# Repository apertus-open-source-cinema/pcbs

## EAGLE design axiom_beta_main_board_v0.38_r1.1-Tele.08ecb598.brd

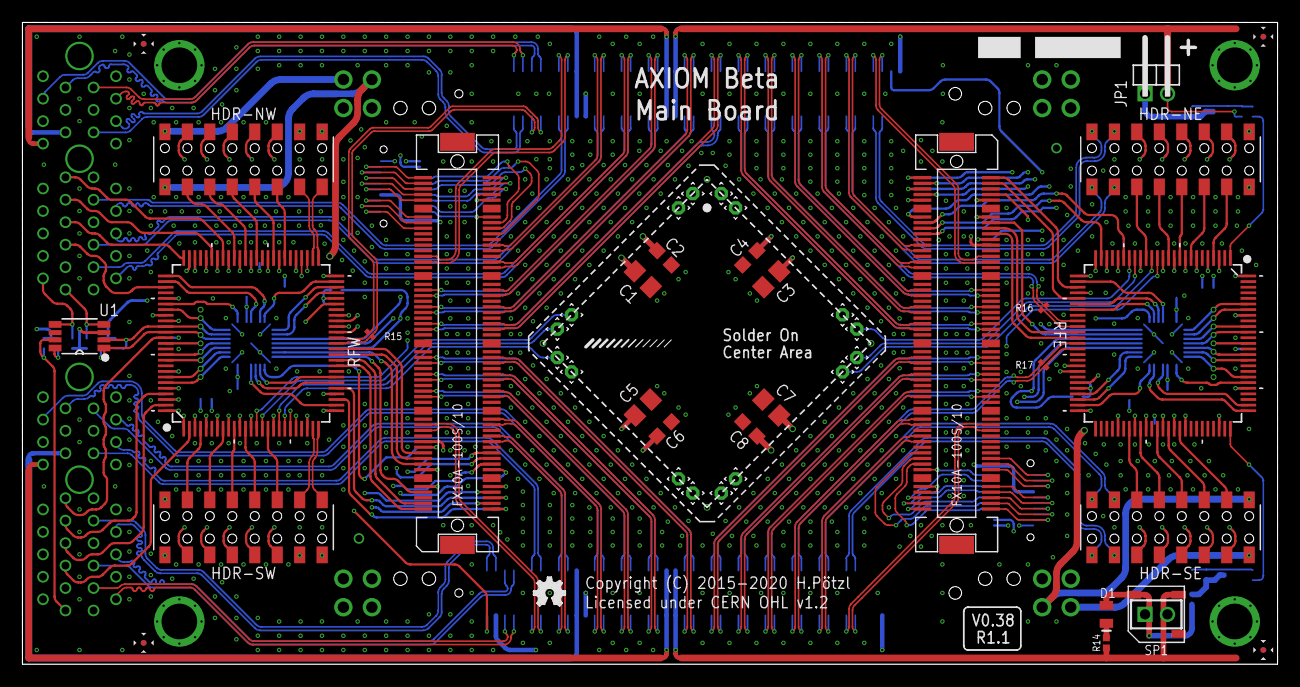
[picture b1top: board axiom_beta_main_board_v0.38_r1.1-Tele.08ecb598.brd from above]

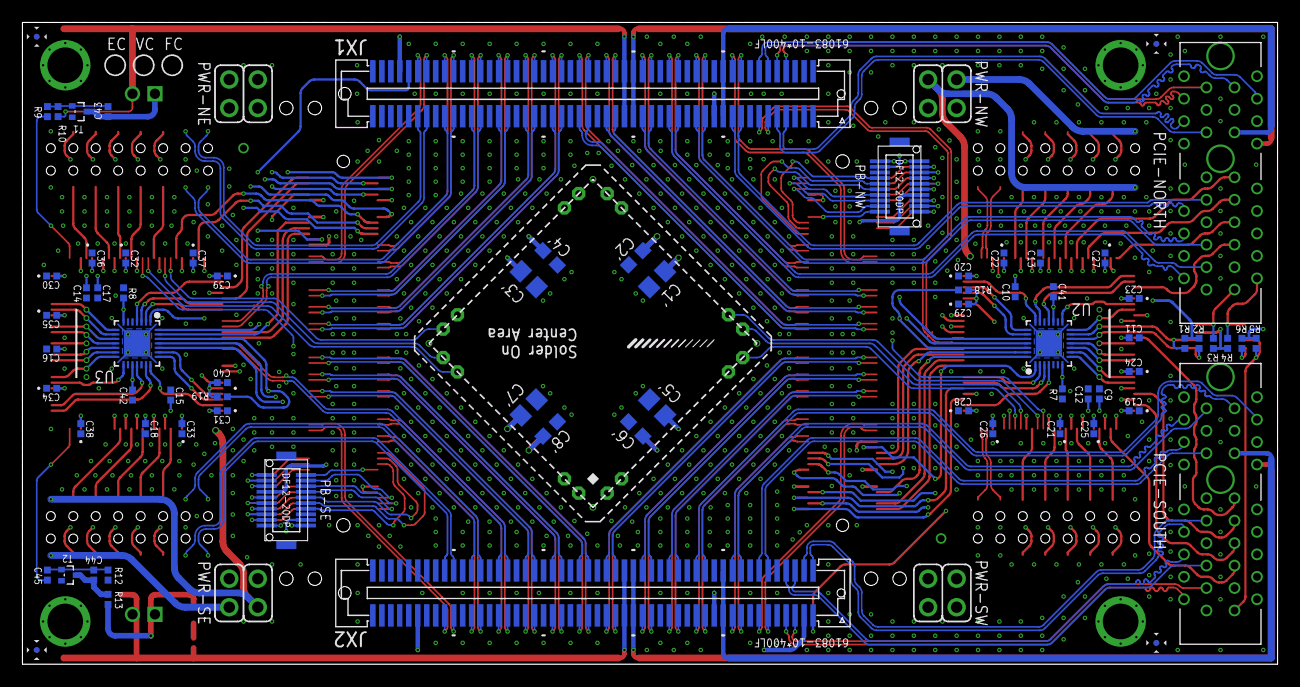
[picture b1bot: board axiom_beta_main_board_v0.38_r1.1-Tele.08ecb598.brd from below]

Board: 4 copper layers, 111.8 x 57.1 mm, 124 parts (78 on the bottom side), 324 nets.

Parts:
C1, C1', C3, C3', C5, C5', C7, C7': 0805-A
C2, C2', C4, C4', C6, C6', C8, C8': 0603-A
C9, C10, C11, C12, C13, C14, C15, C16, C17, C18, C41, C42: 100n; 0402-B
C19, C20, C21, C22, C23, C24, C25, C26, C27, C28, C29, C30, C31, C32, C33, C34, C35, C36, C37, C38, C39, C40, C43, C44: 10n; 0402-B
C45: 1u; 0402-B
D1: DB2S20500L; MICROMELF-R
FID1, FID2, FID3, FID4, FID5, FID6, FID7, FID8: FIDUCIAL; FID_ARROW
HDR-NE: 62101621821
HDR-NW: 62101621821
HDR-SE: 62101621821
HDR-SW: 62101621821
JP1: 1X02M/90-S
JP2: 1X02M
JX1, JX2: BERGSTAK-61083F; 61083-FAKE
LOGO1: OSHW_LOGO_FILLX0100-NT; OSHW_FILLX100_NOTEXT
PAD1, PAD2, PAD3, PAD4, PAD5, PAD6, PAD7, PAD8, PAD9, PAD10, PAD11, PAD12, PAD13, PAD14, PAD15, PAD16: PINPAD1.27MM; 1.2/0.6
PB-NW: DF12(XX)-20DP-0.5V
PB-SE: DF12(XX)-20DP-0.5V
PCIE-NORTH: PCIE-36-AXIOM-NOPEG; PCIE-36-NOPEG
PCIE-SOUTH: PCIE-36-AXIOM-NOPEG; PCIE-36-NOPEG
PWR-NE: PINHD-2X02_2.54; 2X02
PWR-NW: PINHD-2X02_2.54; 2X02
PWR-SE: PINHD-2X02_2.54; 2X02
PWR-SW: PINHD-2X02_2.54; 2X02
R1, R2, R3, R4, R5, R6: 4k7; 0402-B
R7, R8: 50R; 0402-B
R9, R12, R18, R19: 10k; 0402-B
R10: 200k; 0402-B
R13, R14: 12R4; 0402-B
R15, R16, R17: 100R; 0201-B
RFE: MACHXO2-100; MACHXO2-100TQFP
RFW: MACHXO2-100; MACHXO2-100TQFP
SP1: KSSG23J12
T1, T2: NX3008NBKT; SOT416
U1: PCA9540BDP; SOP65P490X300-8N
U2, U3: PIC16F1718-I/MV; QFN40P400X400X55-29N
X-EAST: FX10-100/10S; FX10A-100S/10
X-WEST: FX10-100/10S; FX10A-100S/10
ZED1: µZ-FCI-NOHOLES-R; µZ-NOHOLES-R

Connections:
!E_RESET!: U3.1, X-EAST.19
!SS!_E: RFE.27, U3.4
!SS!_W: RFW.27, U2.4
!W_RESET!: U2.1, X-WEST.19
A_!RST: PB-NW.2, R18.2, U2.26
A_SCL: PB-NW.1, U2.24
A_SDA: PB-NW.3, U2.25
BANK13_00_N: PCIE-NORTH.B17, ZED1.89
BANK13_00_P: PCIE-NORTH.B16, ZED1.87
BANK13_01_N: R15.2, RFW.38, ZED1.90
BANK13_01_P: R15.1, RFW.39, ZED1.88
BANK13_02_N: PCIE-NORTH.A16, ZED1.93
BANK13_02_P: PCIE-NORTH.A17, ZED1.91
BANK13_03_N: PCIE-NORTH.A14, ZED1.94
BANK13_03_P: PCIE-NORTH.A13, ZED1.92
BANK13_04_N: PCIE-SOUTH.A6, ZED1.195
BANK13_04_P: PCIE-SOUTH.A5, ZED1.193
BANK13_05_N: PCIE-SOUTH.A3, ZED1.196
BANK13_05_P: PCIE-SOUTH.A2, ZED1.194
BANK13_06_N: PCIE-SOUTH.A8, ZED1.199
BANK13_06_P: PCIE-SOUTH.A9, ZED1.197
BANK13_SE_0: R7.1, RFW.88, U2.7, ZED1.200
B_!RST: PB-SE.2, R19.2, U3.26
B_SCL: PB-SE.1, U3.24
B_SDA: PB-SE.3, U3.25
CSO_NE_V: C3.1, C3'.1, C4.1, C4'.1, PAD2.1, ZED1.7
CSO_NW_V: C1.1, C1'.1, C2.1, C2'.1, PAD15.1, PWR-NW.1
CSO_SE_V: C7.1, C7'.1, C8.1, C8'.1, PAD7.1, PWR-SE.1
CSO_SW_V: C5.1, C5'.1, C6.1, C6'.1, PAD10.1, ZED1.112
C_CK_E: PAD5.1, RFE.18
C_CK_W: PAD13.1, RFW.18
C_EN_E: PAD3.1, RFE.14
C_EN_W: PAD11.1, RFW.14
C_SI_E: PAD4.1, RFE.19
C_SI_W: PAD12.1, RFW.19
C_SO_E: PAD6.1, RFE.15
C_SO_W: PAD14.1, RFW.15
DONE_E: RFE.76, U3.20
DONE_W: RFW.76, U2.20
E_EN: RFE.20, X-EAST.14
E_I2C_EN: U3.27, X-EAST.13
E_I2C_V: PWR-NE.1, X-EAST.11
E_SCK: RFE.21, X-EAST.12
E_SCL: RFE.36, X-EAST.15
E_SDA: RFE.37, X-EAST.17
E_SDI: RFE.24, X-EAST.16
E_SDO: RFE.25, X-EAST.18
E_SPI_V: PWR-NE.3, X-EAST.21
E_VE_CV: PB-SE.19, X-EAST.90
E_VE_OV: PB-SE.10, X-EAST.93
E_VE_UV: PB-SE.12, X-EAST.91
GND: C1.2, C1'.2, C2.2, C2'.2, C3.2, C3'.2, C4.2, C4'.2, C5.2, C5'.2, C6.2, C6'.2, C7.2, C7'.2, C8.2, C8'.2, C9.2, C10.2, C11.2, C12.2, C13.2, C14.2, C15.2, C16.2, C17.2, C18.2, C19.2, C20.2, C21.2, C22.2, C23.2, C24.2, C25.2, C26.2, C27.2, C28.2, C29.2, C30.2, C31.2, C32.2, C33.2, C34.2, C35.2, C36.2, C37.2, C38.2, C39.2, C40.2, C41.2, C42.2, HDR-NE.1, HDR-NE.2, HDR-SW.1, HDR-SW.2, PAD1.1, PAD8.1, PAD9.1, PAD16.1, PB-NW.5, PB-SE.5, PCIE-NORTH.A1, PCIE-NORTH.A4, PCIE-NORTH.A7, PCIE-NORTH.A10, PCIE-NORTH.A12, PCIE-NORTH.A15, PCIE-NORTH.A18, PCIE-NORTH.B15, PCIE-NORTH.B18, PCIE-SOUTH.A1, PCIE-SOUTH.A4, PCIE-SOUTH.A7, PCIE-SOUTH.A10, PCIE-SOUTH.A12, PCIE-SOUTH.A15, PCIE-SOUTH.A18, PCIE-SOUTH.B15, PCIE-SOUTH.B18, R7.2, R8.2, R12.1, RFE.6, RFE.22, RFE.33, RFE.44, RFE.56, RFE.72, RFE.79, RFE.92, RFW.6, RFW.22, RFW.33, RFW.44, RFW.56, RFW.72, RFW.79, RFW.92, T1.2, T2.2, U1.6, U2.5, U2.16, U2.29, U3.5, U3.16, U3.29, X-EAST.5, X-EAST.20, X-EAST.23, X-EAST.26, X-EAST.29, X-EAST.31, X-EAST.32, X-EAST.37, X-EAST.38, X-EAST.43, X-EAST.44, X-EAST.49, X-EAST.50, X-EAST.51, X-EAST.52, X-EAST.57, X-EAST.58, X-EAST.63, X-EAST.64, X-EAST.69, X-EAST.70, X-EAST.71, X-EAST.76, X-EAST.77, X-EAST.82, X-EAST.G1, X-EAST.G2, X-EAST.G3, X-EAST.G4, X-EAST.G5, X-EAST.G6, X-EAST.G7, X-EAST.G8, X-EAST.G9, X-EAST.G10, X-WEST.5, X-WEST.20, X-WEST.23, X-WEST.26, X-WEST.29, X-WEST.31, X-WEST.32, X-WEST.37, X-WEST.38, X-WEST.43, X-WEST.44, X-WEST.49, X-WEST.50, X-WEST.51, X-WEST.52, X-WEST.57, X-WEST.58, X-WEST.63, X-WEST.64, X-WEST.69, X-WEST.70, X-WEST.71, X-WEST.76, X-WEST.77, X-WEST.82, X-WEST.G1, X-WEST.G2, X-WEST.G3, X-WEST.G4, X-WEST.G5, X-WEST.G6, X-WEST.G7, X-WEST.G8, X-WEST.G9, X-WEST.G10, ZED1.15, ZED1.16, ZED1.21, ZED1.22, ZED1.27, ZED1.28, ZED1.33, ZED1.34, ZED1.39, ZED1.40, ZED1.45, ZED1.46, ZED1.51, ZED1.52, ZED1.65, ZED1.66, ZED1.71, ZED1.72, ZED1.77, ZED1.85, ZED1.86, ZED1.95, ZED1.96, ZED1.115, ZED1.116, ZED1.121, ZED1.122, ZED1.127, ZED1.128, ZED1.133, ZED1.134, ZED1.139, ZED1.140, ZED1.145, ZED1.146, ZED1.151, ZED1.152, ZED1.165, ZED1.166, ZED1.171, ZED1.172, ZED1.177, ZED1.185, ZED1.186, ZED1.191, ZED1.192
INITN_E: RFE.77, U3.18
INITN_W: RFW.77, U2.18
IO_SCL: RFE.86, U3.12
IO_SDA: RFE.85, U3.13
JTAGENB_E: RFE.82, U3.14
JTAGENB_W: RFW.82, U2.14
JTAG_V: PWR-SW.3, X-WEST.21
JX1_00_N: X-EAST.27, ZED1.13
JX1_00_P: X-EAST.25, ZED1.11
JX1_01_N: HDR-NE.13, ZED1.14
JX1_01_P: HDR-NE.15, ZED1.12
JX1_02_N: X-EAST.24, ZED1.19
JX1_02_P: X-EAST.22, ZED1.17
JX1_03_N: HDR-NE.14, ZED1.20
JX1_03_P: HDR-NE.16, ZED1.18
JX1_04_N: X-EAST.30, ZED1.25
JX1_04_P: X-EAST.28, ZED1.23
JX1_05_N: R16.2, RFE.35, ZED1.26
JX1_05_P: R16.1, RFE.34, ZED1.24
JX1_06_N: X-EAST.36, ZED1.31
JX1_06_P: X-EAST.34, ZED1.29
JX1_07_N: X-EAST.35, ZED1.32
JX1_07_P: X-EAST.33, ZED1.30
JX1_08_N: X-EAST.42, ZED1.37
JX1_08_P: X-EAST.40, ZED1.35
JX1_09_N: X-EAST.41, ZED1.38
JX1_09_P: X-EAST.39, ZED1.36
JX1_10_N: X-EAST.48, ZED1.43
JX1_10_P: X-EAST.46, ZED1.41
JX1_11_N: X-EAST.47, ZED1.44
JX1_11_P: X-EAST.45, ZED1.42
JX1_12_N: X-WEST.56, ZED1.49
JX1_12_P: X-WEST.54, ZED1.47
JX1_13_N: X-WEST.55, ZED1.50
JX1_13_P: X-WEST.53, ZED1.48
JX1_14_N: X-WEST.62, ZED1.55
JX1_14_P: X-WEST.60, ZED1.53
JX1_15_N: X-WEST.61, ZED1.56
JX1_15_P: X-WEST.59, ZED1.54
JX1_16_N: X-WEST.68, ZED1.63
JX1_16_P: X-WEST.66, ZED1.61
JX1_17_N: X-WEST.67, ZED1.64
JX1_17_P: X-WEST.65, ZED1.62
JX1_18_N: X-WEST.74, ZED1.69
JX1_18_P: X-WEST.72, ZED1.67
JX1_19_N: PCIE-NORTH.A3, ZED1.70
JX1_19_P: PCIE-NORTH.A2, ZED1.68
JX1_20_N: X-WEST.80, ZED1.75
JX1_20_P: X-WEST.78, ZED1.73
JX1_21_N: PCIE-NORTH.A6, ZED1.76
JX1_21_P: PCIE-NORTH.A5, ZED1.74
JX1_22_N: X-WEST.75, ZED1.83
JX1_22_P: X-WEST.73, ZED1.81
JX1_23_N: PCIE-NORTH.A9, ZED1.84
JX1_23_P: PCIE-NORTH.A8, ZED1.82
JX1_SE_0: R8.1, RFE.88, U3.7, ZED1.9
JX2_00_N: HDR-SE.14, ZED1.119
JX2_00_P: HDR-SE.16, ZED1.117
JX2_01_N: X-EAST.73, ZED1.120
JX2_01_P: X-EAST.75, ZED1.118
JX2_02_N: HDR-SE.13, ZED1.125
JX2_02_P: HDR-SE.15, ZED1.123
JX2_03_N: X-EAST.78, ZED1.126
JX2_03_P: X-EAST.80, ZED1.124
JX2_04_N: R17.1, RFE.38, ZED1.131
JX2_04_P: R17.2, RFE.39, ZED1.129
JX2_05_N: X-EAST.72, ZED1.132
JX2_05_P: X-EAST.74, ZED1.130
JX2_06_N: X-EAST.65, ZED1.137
JX2_06_P: X-EAST.67, ZED1.135
JX2_07_N: X-EAST.66, ZED1.138
JX2_07_P: X-EAST.68, ZED1.136
JX2_08_N: X-EAST.59, ZED1.143
JX2_08_P: X-EAST.61, ZED1.141
JX2_09_N: X-EAST.60, ZED1.144
JX2_09_P: X-EAST.62, ZED1.142
JX2_10_N: X-EAST.53, ZED1.149
JX2_10_P: X-EAST.55, ZED1.147
JX2_11_N: X-EAST.54, ZED1.150
JX2_11_P: X-EAST.56, ZED1.148
JX2_12_N: X-WEST.45, ZED1.155
JX2_12_P: X-WEST.47, ZED1.153
JX2_13_N: X-WEST.46, ZED1.156
JX2_13_P: X-WEST.48, ZED1.154
JX2_14_N: X-WEST.39, ZED1.163
JX2_14_P: X-WEST.41, ZED1.161
JX2_15_N: X-WEST.40, ZED1.164
JX2_15_P: X-WEST.42, ZED1.162
JX2_16_N: X-WEST.33, ZED1.169
JX2_16_P: X-WEST.35, ZED1.167
JX2_17_N: X-WEST.34, ZED1.170
JX2_17_P: X-WEST.36, ZED1.168
JX2_18_N: PCIE-SOUTH.B17, ZED1.175
JX2_18_P: PCIE-SOUTH.B16, ZED1.173
JX2_19_N: X-WEST.28, ZED1.176
JX2_19_P: X-WEST.30, ZED1.174
JX2_20_N: PCIE-SOUTH.A17, ZED1.183
JX2_20_P: PCIE-SOUTH.A16, ZED1.181
JX2_21_N: X-WEST.22, ZED1.184
JX2_21_P: X-WEST.24, ZED1.182
JX2_22_N: PCIE-SOUTH.A13, ZED1.189
JX2_22_P: PCIE-SOUTH.A14, ZED1.187
JX2_23_N: X-WEST.25, ZED1.190
JX2_23_P: X-WEST.27, ZED1.188
unnamed: C43.2, JP1.1, T1.3
unnamed: C44.2, R13.1, T2.3
unnamed: D1.C, R14.1
unnamed: D1.A, JP2.1, R13.2, SP1.2
unnamed: C43.1, R9.2, R10.2, T1.1
unnamed: C44.1, C45.1, R12.2, T2.1
N_CHK_V: PB-NW.14, X-WEST.92
N_I2C_EN: U3.28, X-EAST.7
N_I2C_V: PWR-NE.4, X-EAST.9
N_IO0: R9.1, RFE.1
N_SCK: RFE.42, X-EAST.2
N_SCL: RFE.28, X-EAST.1
N_SDA: RFE.30, X-EAST.3
N_SDI: RFE.29, X-EAST.6
N_SDO: RFE.43, X-EAST.4
N_SPI_EN: RFE.45, X-EAST.8
N_SPI_V: PWR-NE.2, X-EAST.10
N_VE_CV: PB-NW.17, X-WEST.96
N_VE_OV: PB-NW.8, X-WEST.95
N_VE_RS: PB-NW.7, X-WEST.88
N_VE_UV: PB-NW.20, X-WEST.85
N_VN_CV: PB-NW.15, X-WEST.98
N_VN_OV: PB-NW.6, X-WEST.97
N_VN_RS: PB-NW.11, X-WEST.86
N_VN_UV: PB-NW.18, X-WEST.87
N_VW_CV: PB-NW.13, X-WEST.100
N_VW_OV: PB-NW.4, X-WEST.99
N_VW_RS: PB-NW.9, X-WEST.84
N_VW_UV: PB-NW.16, X-WEST.89
PB22B_E: RFE.47, U3.23
PB22B_W: RFW.47, U2.23
PCIE_I2C_V: PCIE-NORTH.B3, PCIE-SOUTH.B3, R3.1, R4.1, R5.1, R6.1, U1.3, ZED1.198
PCIE_N_5V: PCIE-NORTH.B12, ZED1.59, ZED1.60
PCIE_N_IO0: PCIE-NORTH.B4, RFW.83
PCIE_N_IO1: PCIE-NORTH.B5, RFW.78
PCIE_N_IO2: PCIE-NORTH.B6, RFW.74
PCIE_N_IO3: PCIE-NORTH.B7, RFW.75
PCIE_N_IO4: PCIE-NORTH.B8, RFW.71
PCIE_N_IO5: PCIE-NORTH.B9, RFW.70
PCIE_N_IO6: PCIE-NORTH.B10, RFW.69
PCIE_N_IO7: PCIE-NORTH.B11, RFW.68
PCIE_N_SCL: PCIE-NORTH.B2, R4.2, U1.5
PCIE_N_SDA: PCIE-NORTH.B1, R3.2, U1.4
PCIE_N_V: PCIE-NORTH.B13, ZED1.79, ZED1.80
PCIE_N_VCCIO: PCIE-NORTH.B14, ZED1.78
PCIE_SCL: R2.2, RFW.86, U1.1, U2.12
PCIE_SDA: R1.2, RFW.85, U1.2, U2.13
PCIE_S_5V: PCIE-SOUTH.B12, ZED1.159, ZED1.160
PCIE_S_IO0: PCIE-SOUTH.B4, RFW.1
PCIE_S_IO1: PCIE-SOUTH.B5, RFW.2
PCIE_S_IO2: PCIE-SOUTH.B6, RFW.98
PCIE_S_IO3: PCIE-SOUTH.B7, RFW.99
PCIE_S_IO4: PCIE-SOUTH.B8, RFW.96
PCIE_S_IO5: PCIE-SOUTH.B9, RFW.97
PCIE_S_IO6: PCIE-SOUTH.B10, RFW.84
PCIE_S_IO7: PCIE-SOUTH.B11, RFW.87
PCIE_S_SCL: PCIE-SOUTH.B2, R6.2, U1.8
PCIE_S_SDA: PCIE-SOUTH.B1, R5.2, U1.7
PCIE_S_V: PCIE-SOUTH.B13, ZED1.179, ZED1.180
PCIE_S_VCCIO: PCIE-SOUTH.B14, ZED1.178
PEX_N_V: JP1.2, R10.1, ZED1.57, ZED1.58
PEX_S_V: JP2.2, R14.2, SP1.1, ZED1.157, ZED1.158
PROGRAMN_E: RFE.81, U3.15
PROGRAMN_W: RFW.81, U2.15
RFAB_E_V: C14.1, C15.1, C30.1, C31.1, PWR-SE.3, RFE.50, RFE.100
RFAB_W_V: C9.1, C10.1, C19.1, C20.1, PWR-NW.3, RFW.50, RFW.100
SCK_E: RFE.31, U3.3
SCK_W: RFW.31, U2.3
SDI_E: RFE.49, U3.21
SDI_W: RFW.49, U2.21
SDO_E: RFE.32, U3.2
SDO_W: RFW.32, U2.2
SH_NE_IO0: HDR-NE.4, RFE.4
SH_NE_IO1: HDR-NE.3, RFE.3
SH_NE_IO2: HDR-NE.6, RFE.8
SH_NE_IO3: HDR-NE.5, RFE.7
SH_NE_IO4: HDR-NE.8, RFE.10
SH_NE_IO5: HDR-NE.7, RFE.9
SH_NE_IO6: HDR-NE.10, RFE.12
SH_NE_IO7: HDR-NE.9, RFE.13
SH_NE_IO8: HDR-NE.12, RFE.16
SH_NE_IO9: HDR-NE.11, RFE.17
SH_NW_IO0: HDR-NW.4, RFW.67
SH_NW_IO1: HDR-NW.3, RFW.66
SH_NW_IO2: HDR-NW.6, RFW.65
SH_NW_IO3: HDR-NW.5, RFW.64
SH_NW_IO4: HDR-NW.8, RFW.63
SH_NW_IO5: HDR-NW.7, RFW.62
SH_NW_IO6: HDR-NW.10, RFW.60
SH_NW_IO7: HDR-NW.9, RFW.59
SH_NW_IO8: HDR-NW.12, RFW.58
SH_NW_IO9: HDR-NW.11, RFW.57
SH_NW_V: HDR-NW.2, PWR-NW.4
SH_NW_VIO: C11.1, C12.1, C13.1, C21.1, C22.1, C23.1, C24.1, C25.1, C26.1, C27.1, C28.1, C29.1, C41.1, HDR-NW.1, PWR-NW.2, R1.1, R2.1, R18.1, RFW.5, RFW.11, RFW.23, RFW.26, RFW.46, RFW.55, RFW.73, RFW.80, RFW.93, U2.17
SH_SE_IO0: HDR-SE.4, RFE.67
SH_SE_IO1: HDR-SE.3, RFE.66
SH_SE_IO2: HDR-SE.6, RFE.65
SH_SE_IO3: HDR-SE.5, RFE.64
SH_SE_IO4: HDR-SE.8, RFE.63
SH_SE_IO5: HDR-SE.7, RFE.62
SH_SE_IO6: HDR-SE.10, RFE.60
SH_SE_IO7: HDR-SE.9, RFE.59
SH_SE_IO8: HDR-SE.12, RFE.58
SH_SE_IO9: HDR-SE.11, RFE.57
SH_SE_V: HDR-SE.2, PWR-SE.4
SH_SE_VIO: C16.1, C17.1, C18.1, C32.1, C33.1, C34.1, C35.1, C36.1, C37.1, C38.1, C39.1, C40.1, C42.1, HDR-SE.1, PWR-SE.2, R19.1, RFE.5, RFE.11, RFE.23, RFE.26, RFE.46, RFE.55, RFE.73, RFE.80, RFE.93, U3.17
SH_SW_IO0: HDR-SW.4, RFW.4
SH_SW_IO1: HDR-SW.3, RFW.3
SH_SW_IO2: HDR-SW.6, RFW.8
SH_SW_IO3: HDR-SW.5, RFW.7
SH_SW_IO4: HDR-SW.8, RFW.10
SH_SW_IO5: HDR-SW.7, RFW.9
SH_SW_IO6: HDR-SW.10, RFW.12
SH_SW_IO7: HDR-SW.9, RFW.13
SH_SW_IO8: HDR-SW.12, RFW.16
SH_SW_IO9: HDR-SW.11, RFW.17
SN_E: RFE.48, U3.22
SN_W: RFW.48, U2.22
S_CHK_V: PB-SE.14, X-EAST.92
S_I2C_EN: U2.28, X-WEST.7
S_I2C_V: PWR-SW.4, X-WEST.9
S_IO0: C45.2, RFE.75
S_SCK: RFW.28, X-WEST.2
S_SCL: RFW.34, X-WEST.1
S_SDA: RFW.35, X-WEST.3
S_SDI: RFW.30, X-WEST.6
S_SDO: RFW.29, X-WEST.4
S_SPI_EN: RFW.45, X-WEST.8
S_SPI_V: PWR-SW.2, X-WEST.10
S_VE_CV: PB-SE.13, X-EAST.100
S_VE_OV: PB-SE.4, X-EAST.99
S_VE_RS: PB-SE.9, X-EAST.84
S_VE_UV: PB-SE.16, X-EAST.89
S_VS_CV: PB-SE.15, X-EAST.98
S_VS_OV: PB-SE.6, X-EAST.97
S_VS_RS: PB-SE.11, X-EAST.86
S_VS_UV: PB-SE.18, X-EAST.87
S_VW_CV: PB-SE.17, X-EAST.96
S_VW_OV: PB-SE.8, X-EAST.95
S_VW_RS: PB-SE.7, X-EAST.88
S_VW_UV: PB-SE.20, X-EAST.85
TCK: RFW.43, X-WEST.12
TCK_E: RFE.91, U3.10
TCK_W: RFW.91, U2.10
TDI: RFW.41, X-WEST.16
TDI_E: RFE.94, U3.9
TDI_W: RFW.94, U2.9
TDO: RFW.40, X-WEST.18
TDO_E: RFE.95, U3.8
TDO_W: RFW.95, U2.8
TMS: RFW.42, X-WEST.14
TMS_E: RFE.90, U3.11
TMS_W: RFW.90, U2.11
W_I2C_EN: U2.27, X-WEST.13
W_I2C_V: PWR-SW.1, X-WEST.11
W_SCL: RFW.36, X-WEST.15
W_SDA: RFW.37, X-WEST.17
W_VW_CV: PB-NW.19, X-WEST.90
W_VW_OV: PB-NW.10, X-WEST.93
W_VW_UV: PB-NW.12, X-WEST.91
XX1_N: HDR-NW.13, RFW.52
XX1_P: HDR-NW.15, RFW.51
XX2_N: HDR-NW.14, RFW.54
XX2_P: HDR-NW.16, RFW.53
XX3_N: HDR-SW.16, RFW.25
XX3_P: HDR-SW.14, RFW.24
XX4_N: HDR-SW.15, RFW.21
XX4_P: HDR-SW.13, RFW.20

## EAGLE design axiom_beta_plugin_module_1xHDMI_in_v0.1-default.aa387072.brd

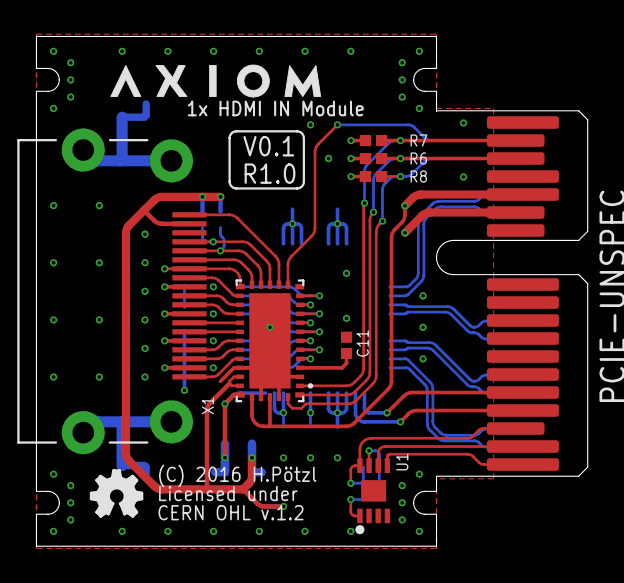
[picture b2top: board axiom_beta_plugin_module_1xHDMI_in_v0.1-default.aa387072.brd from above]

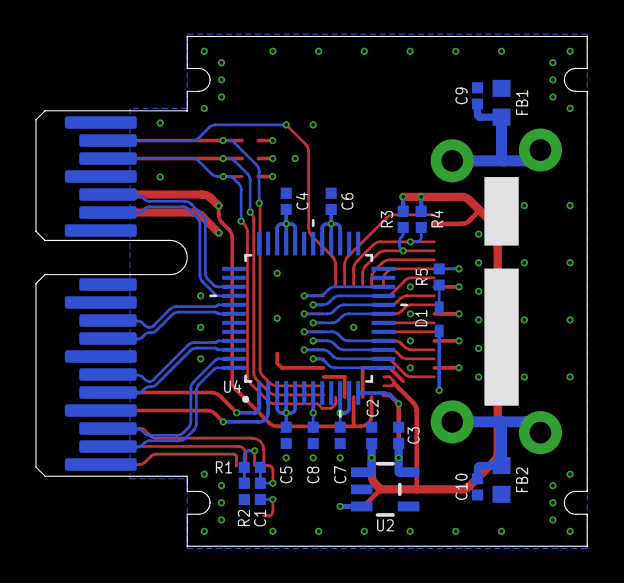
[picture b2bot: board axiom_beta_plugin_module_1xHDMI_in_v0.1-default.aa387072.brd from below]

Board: 4 copper layers, 30.6 x 28.3 mm, 30 parts (20 on the bottom side), 48 nets.

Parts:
C1, C4, C5: 100n; 0402-B
C2, C3: 1u; 0402-B
C6, C7, C8, C9, C10, C11: 10n; 0402-B
D1: SOD523
FB1, FB2: 0603-B
LOGO2: OSHW_LOGO_FILLX0100-NT; OSHW_FILLX100_NOTEXT
PCIE-UNSPEC: PCIE-36-AXIOM
R1: 10k; 0402-B
R2: 1k; 0402-B
R3, R4, R5, R6, R7, R8: 0402-B
U1: BR24G04NUX; DFN200X300X100-9N
U2: AP7331-FIXEDSOT23-5; SOT23-5
U3: HDMI2C2-14HD; QFN50P650L90W-25N
U4: DS90LV004; QFP50P900X900X160-48N
U$: AXIOM_LOGO459X70; AXIOM_LOGO_459X70
X1: HDMI-10029449; 10029449-X01XLF

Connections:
3V3: C4.1, C5.1, C6.1, C7.1, C8.1, PCIE-UNSPEC.B13, U4.3, U4.4, U4.5, U4.7, U4.10, U4.11, U4.27, U4.28, U4.29, U4.32, U4.33, U4.34
5V_IN: C2.1, R3.1, R4.1, U2.1, U2.3, U3.28, U3.29, X1.18
CEC: PCIE-UNSPEC.A16, R8.2, U3.35
CK+: U3.20, X1.10
CK-: U3.19, X1.12
D0+: U3.22, X1.7
D0-: U3.21, X1.9
D1+: U3.24, X1.4
D1-: U3.23, X1.6
D2+: U3.26, X1.1
D2-: U3.25, X1.3
DDC_SCL: PCIE-UNSPEC.B16, R6.2, U3.36
DDC_SDA: PCIE-UNSPEC.B17, R7.2, U3.1
GND: C1.2, C2.2, C3.2, C4.2, C5.2, C6.2, C7.2, C8.2, C9.2, C10.2, C11.2, FB1.2, FB2.2, PCIE-UNSPEC.A1, PCIE-UNSPEC.A4, PCIE-UNSPEC.A7, PCIE-UNSPEC.A10, PCIE-UNSPEC.A12, PCIE-UNSPEC.A15, PCIE-UNSPEC.A18, PCIE-UNSPEC.B15, PCIE-UNSPEC.B18, R2.2, U1.1, U1.2, U1.3, U1.4, U1.EP, U2.2, U3.2, U3.27, U3.32, U3.34, U3.EP, U4.8, U4.9, U4.17, U4.18, U4.23, U4.24, U4.25, U4.26, U4.37, U4.38, U4.43, U4.44, X1.2, X1.5, X1.8, X1.11, X1.17
HPD: PCIE-UNSPEC.A17, U3.13
I2C_V: C1.1, PCIE-UNSPEC.B3, R1.1, U1.8
IN0+: U3.4, U4.13
IN0-: U3.5, U4.14
IN1+: U3.6, U4.15
IN1-: U3.7, U4.16
IN2+: U3.8, U4.19
IN2-: U3.9, U4.20
IN3+: U3.10, U4.21
IN3-: U3.11, U4.22
LVDS_0_N: PCIE-UNSPEC.A3, U4.47
LVDS_0_P: PCIE-UNSPEC.A2, U4.48
LVDS_1_N: PCIE-UNSPEC.A6, U4.45
LVDS_1_P: PCIE-UNSPEC.A5, U4.46
LVDS_2_N: PCIE-UNSPEC.A9, U4.41
LVDS_2_P: PCIE-UNSPEC.A8, U4.42
LVDS_3_N: PCIE-UNSPEC.A14, U4.39
LVDS_3_P: PCIE-UNSPEC.A13, U4.40
unnamed: R3.2, U3.16, X1.15
unnamed: R4.2, U3.15, X1.16
unnamed: R5.2, U3.18, X1.13
unnamed: U3.17, X1.14
unnamed: U3.14, X1.19
unnamed: C9.1, FB1.1, X1.Z1, X1.Z2
unnamed: R1.2, R2.1, U1.7
unnamed: C10.1, FB2.1, X1.Z3, X1.Z4
unnamed: D1.C, R5.1
unnamed: C11.1, U3.3
PEM0: PCIE-UNSPEC.B5, U4.1
PEM1: PCIE-UNSPEC.B4, U4.2
SCL: PCIE-UNSPEC.B2, U1.6
SDA: PCIE-UNSPEC.B1, U1.5
VDD_CEC: C3.1, D1.A, U2.5, U3.30, U4.12
VDD_IC: PCIE-UNSPEC.B14, R6.1, R7.1, R8.1, U3.31, U3.33

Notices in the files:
axiom_beta_main_board_v0.38_r1.1-Tele.08ecb598.brd:
Copyright (C) 2015-2020 H.Pötzl
Licensed under CERN OHL v1.2
axiom_beta_plugin_module_1xHDMI_in_v0.1-default.aa387072.brd:
(C) 2016 H.Pötzl
CERN OHL v.1.2
